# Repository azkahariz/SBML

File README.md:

# Advanced Microcontroller Based Systems

## Table of Contents
1. [A short summary](#advanced-microcontroller-based-systems)
2. [Schematic and 3D Design](#schematic-and-3d-design)
    1. [Schematic](#schematic)
    2. [3D Design](#3d-design)
3. [Demo Project](#demo-project)

This project aims to create an ESP-IDF Audio Player using Internet Radio. The main project is located in the [**using_arduino_package**](/tree/main/using_arduino_package) folder, which adds the Arduino package to the ESP-IDF component, allowing coding with the Arduino approach.

Currently, I am **in the process** of constructing a web radio using ESP-IDF not incorporating ESP-ADF. The procedure is laid out as follows:

1. Construct a client-to-server relationship (access point/router)
2. Putting together the I2S interface
3. Establish an internet streaming link to the host
4. Broadcasting audio (internet streaming) by way of the I2S protocol to the audio system
5. Preserve the web streaming audio connection intact.

The instructions for step 1 can be found in the [**connect_wifi_v1**](https://github.com/azkahariz/SBML/tree/main/connect_wifi_v1), while the instructions for step 2 can be found in the [**build-project-01**](https://github.com/azkahariz/SBML/tree/main/build-project-01). For step 4, the preliminary result is that the ESP-IDF can generate the desired sound, such as a chicken alarm sound. This can then be developed so that the ESP-IDF can output streaming audio. The results can be viewed in the [**SPIFFS**](https://github.com/azkahariz/SBML/tree/main/SPIFFS).

# Schematic and 3D Design
This section will explain the schematic and 3D design employed.
## Schematic

In this project, the **ESP32 Devkit V1**, **MAX98357A**, and **8 Ohm speakers** were utilized. The ESP32 Devkit V1 is used to manage the MAX98357A and 8 Ohm speakers. The MAX98357A transforms digital signals into analog signals, while the 8 Ohm speakers are employed to play audio signals.

A schematic was created and assembled on a breadboard as illustrated below.

## 3D Design

The schematic design can be used to create a circuit board, as illustrated in the image below. The components are placed in specific positions and the copper circuit paths are established.

The image below illustrates the 3D design view of the circuit board, featuring the front view, side view, and top view.

Schematics and 3D design can be seen in the [**KiCAD_file**](https://github.com/azkahariz/SBML/tree/main/KiCAD_file) folder. This folder contains the circuit boards, components, and 3D models for the project.

# Demo Project
You can see this demo project in this YouTube [link](https://youtu.be/mOV-Ywjk-ak).

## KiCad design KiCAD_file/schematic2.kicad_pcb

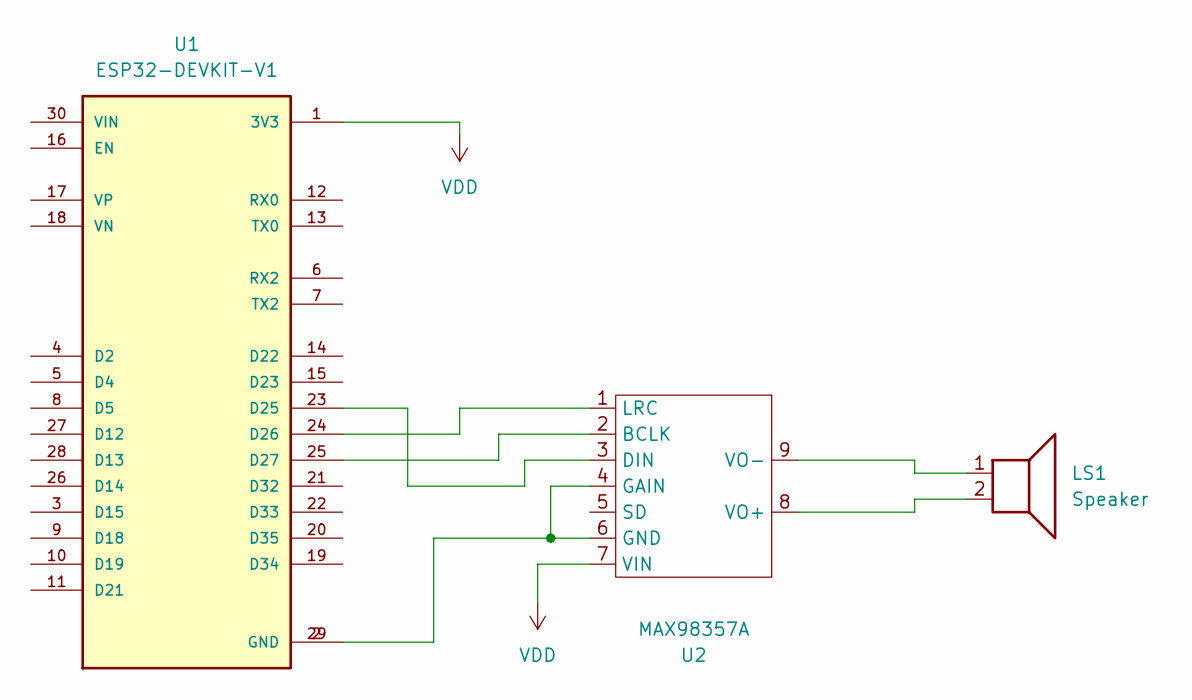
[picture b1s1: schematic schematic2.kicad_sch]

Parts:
LS1: Speaker
U1: ESP32-DEVKIT-V1; MODULE_ESP32-DEVKIT_V1; PARTREV N/A
U2: MAX98357A; MAX98357A_board

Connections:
unnamed: U1.2 (GND), U1.29 (GND), U2.4 (GAIN), U2.6 (GND)
unnamed: U1.23 (D25), U2.3 (DIN)
unnamed: U1.24 (D26), U2.1 (LRC)
unnamed: U1.25 (D27), U2.2 (BCLK)
unnamed: LS1.2, U2.8 (VO+)
unnamed: LS1.1, U2.9 (VO-)
VDD: U1.1 (3V3), U2.7 (VIN)

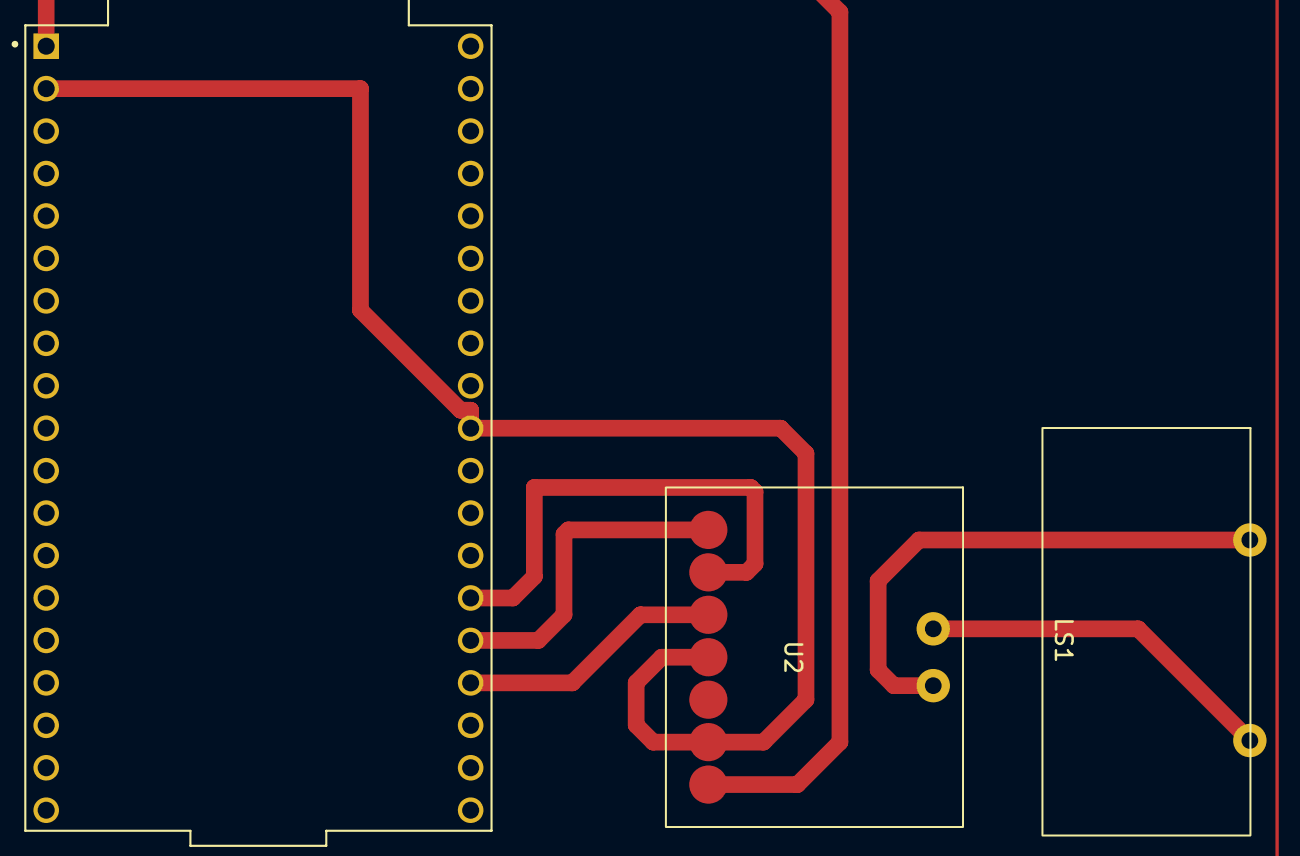
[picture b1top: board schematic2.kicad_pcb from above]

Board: 2 copper layers, 3 parts (0 on the bottom side), 7 nets.

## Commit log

2022-12-29 Rename using_arduino_package/main/components/.gitignore to using_arduino_package/main/components/arduino/.gitignore
2022-12-29 Create sdkconfig
2022-12-29 Rename using_arduino_package/main/components/arduino/tools/sdk/esp32/.gitignore to using_arduino_package/main/components/arduino/tools/sdk/esp32/lib/.gitignore
2022-12-30 Moved the Component folder because it was in the wrong location.
2022-12-30 Update libraries
2022-12-30 Your branch is up to date with 'origin/main'.
2022-12-30 modified README.md
2022-12-30 add esp32-arduino-lib-builder and .vscode
2022-12-30 deleted esp32-arduino-lib-builder
2022-12-30 deleted: using_arduino_package/esp32-arduino-lib-builder
2022-12-30 SPIIFFs
2022-12-30 WiFi Connect folder
2022-12-30 Add KiCAD_file
2022-12-30 modified README
2022-12-30 add video
2022-12-30 Add demo project
2022-12-30 edit video frame
